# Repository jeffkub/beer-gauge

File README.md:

# beer-gauge
Digital scale with display for weighing beer left in a keg/kegerator

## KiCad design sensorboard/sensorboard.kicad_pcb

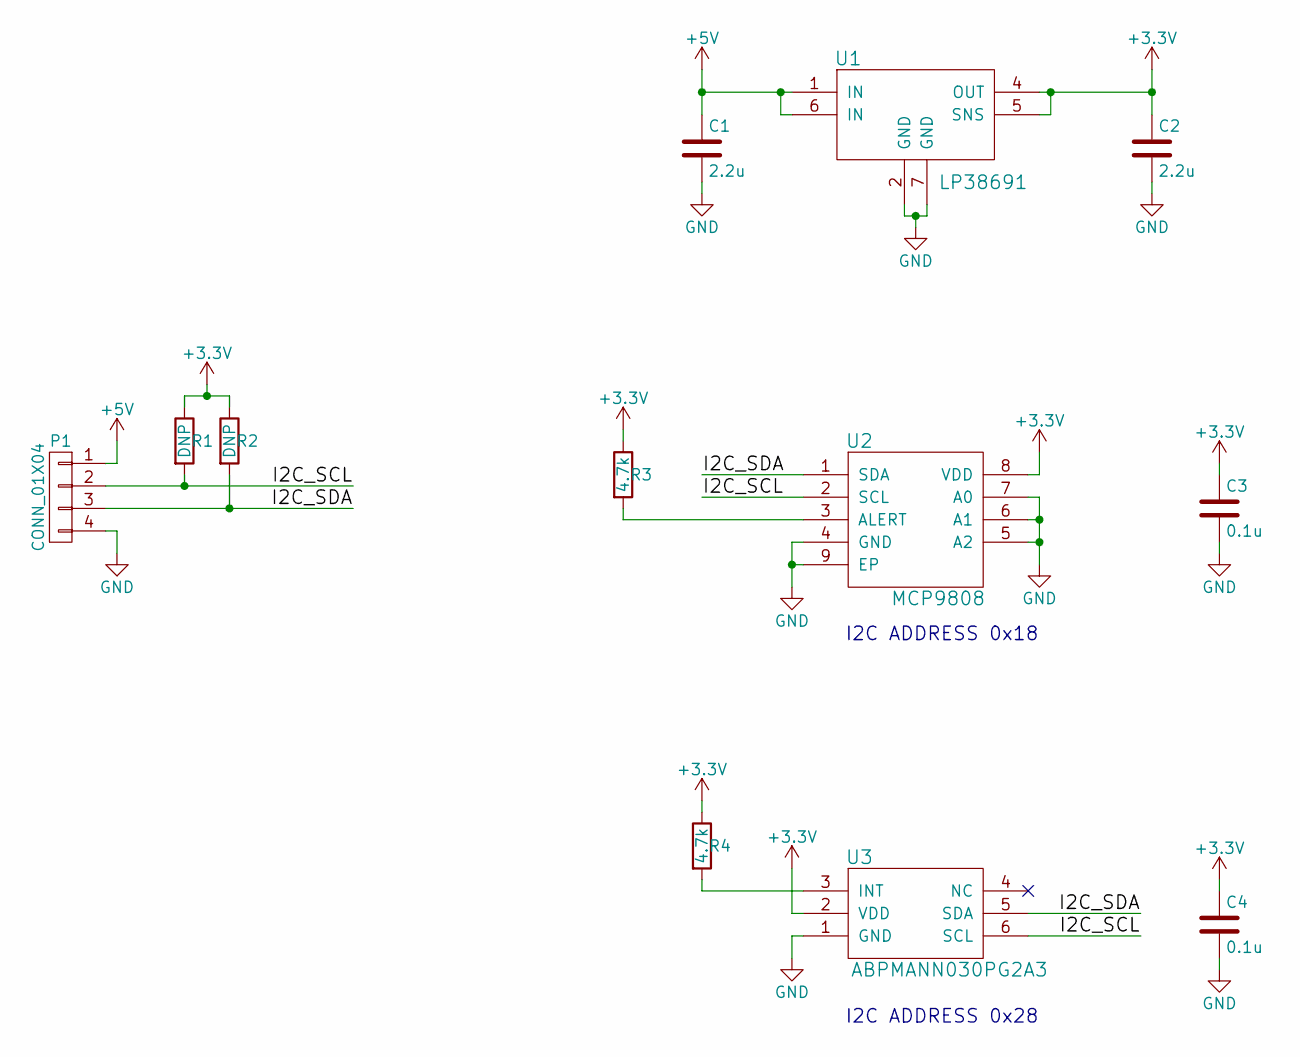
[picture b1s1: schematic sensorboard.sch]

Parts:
C1, C2: 2.2u; C_0603
C3, C4: 0.1u; C_0603
P1: CONN_01X04; 0855025005
R1, R2: DNP; R_0603
R3, R4: 4.7k; R_0603
U1: LP38691; DFN-6-1EP_3x3mm_Pitch0.95mm
U2: MCP9808; DFN-8-1EP_3x2mm_Pitch0.5mm
U3: ABPMANN030PG2A3

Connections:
+3V3: C2.1, C3.1, C4.1, R1.1, R2.1, R3.1, R4.1, U1.4 (OUT), U1.5 (SNS), U2.8 (VDD), U3.2 (VDD)
+5V: C1.1, P1.1, U1.1 (IN), U1.6 (IN)
/I2C_SCL: P1.2, R1.2, U2.2 (SCL), U3.6 (SCL)
/I2C_SDA: P1.3, R2.2, U2.1 (SDA), U3.5 (SDA)
GND: C1.2, C2.2, C3.2, C4.2, P1.4, U1.2 (GND), U1.7 (GND), U2.4 (GND), U2.5 (A2), U2.6 (A1), U2.7 (A0), U2.9 (EP), U3.1 (GND)
unnamed: R3.2, U2.3 (ALERT)
unnamed: R4.2, U3.3 (INT)

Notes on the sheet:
I2C ADDRESS 0x18
I2C ADDRESS 0x28

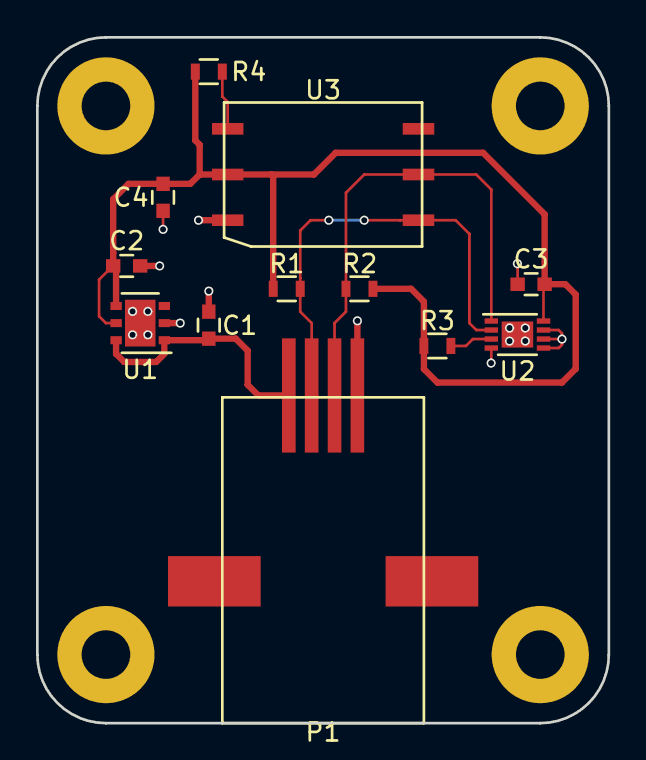
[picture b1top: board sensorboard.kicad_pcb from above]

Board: 2 copper layers, 31.8 x 38.1 mm, 12 parts (0 on the bottom side), 7 nets.

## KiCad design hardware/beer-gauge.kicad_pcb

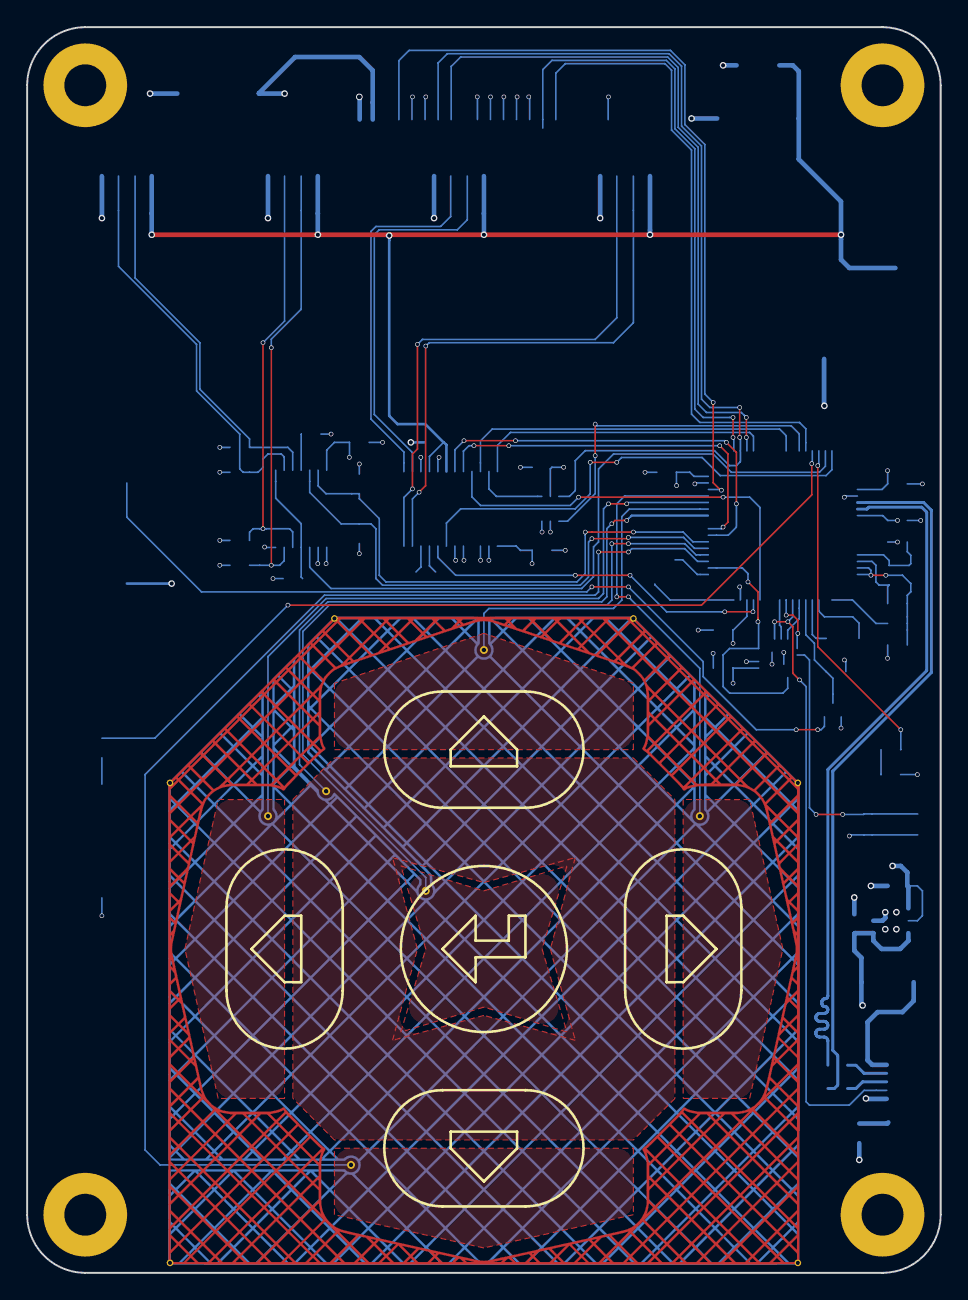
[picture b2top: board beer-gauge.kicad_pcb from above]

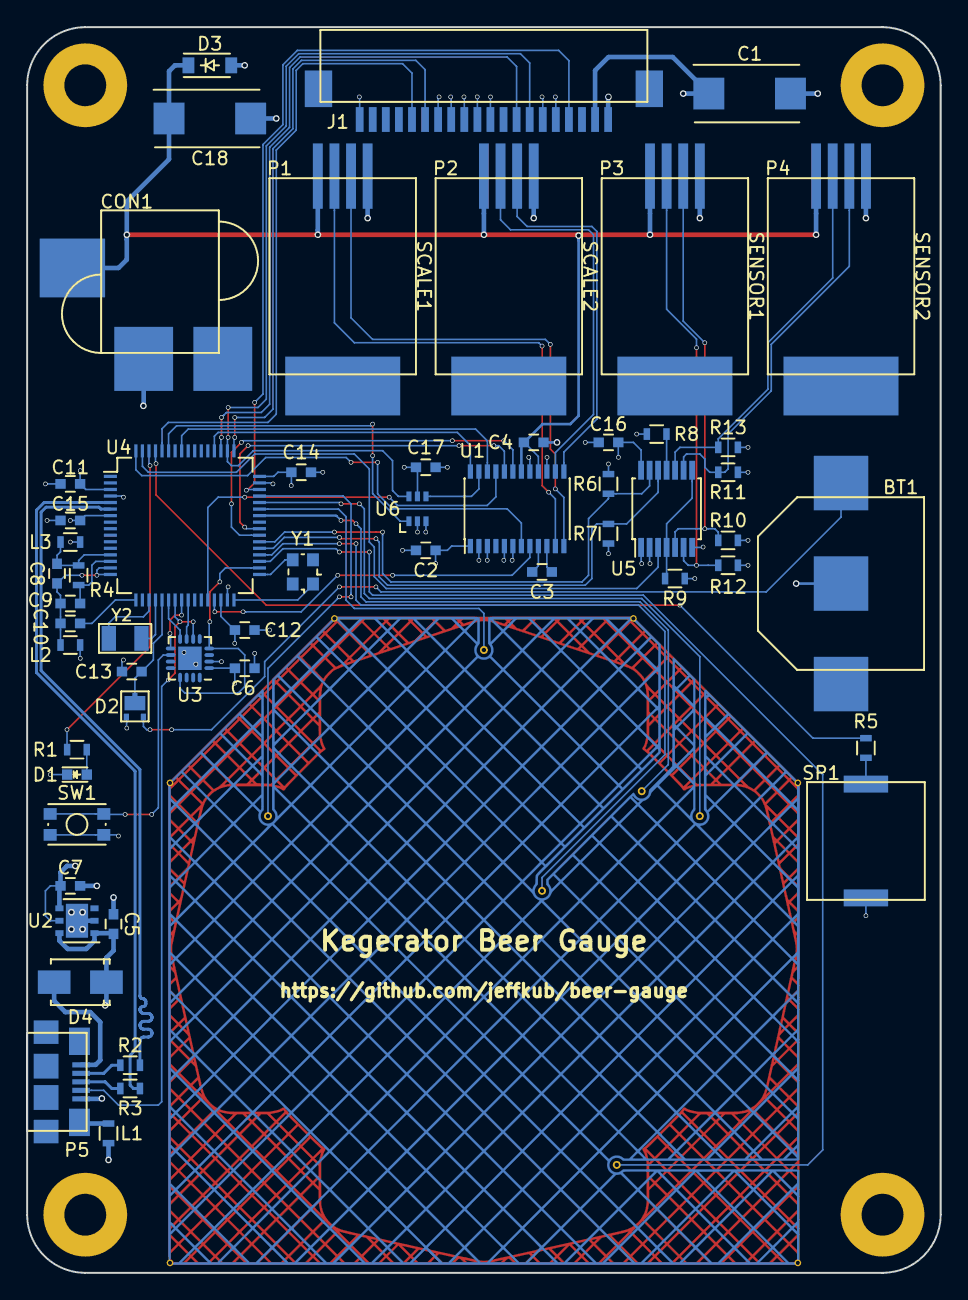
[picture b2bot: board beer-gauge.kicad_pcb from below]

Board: 4 copper layers, 69.8 x 95.2 mm, 62 parts (56 on the bottom side), 64 nets.

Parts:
BT1: Battery; BK-885
C1: 220u; TantalC_SizeD_EIA-7343_Reflow
C2, C3, C4, C6, C9, C10, C11, C12, C13, C14, C16, C17: 0.1u; C_0603
C5, C7, C8, C15: 2.2u; C_0603
C18: 100u; TantalC_SizeD_EIA-7343_Reflow
CON1: BARREL_JACK; PJ-070AH-SMT
D1: LED; LED_0603
D2: PMEG4010CPA; SOT1061
D3: DDZ6V2B; SOD-123
D4: S1B; SMA_Standard
J1: OLED_MODULE; 0522712069
L1, L3: 600 Ohm/100 MHz; R_0603
L2: 600 Ohm/100 Mhz; R_0603
P1, P2, P3, P4: CONN_01X04; 0855135016
P5: USB_OTG; 10118192
R1, R4, R5: 470; R_0603
R2, R3: 33; R_0603
R6, R7, R8, R9, R10, R11, R12, R13: 4.7k; R_0603
SP1: PIEZO; PKMCS
SW1: SW_PUSH; SW_SPST_KMR2
U1: ADS1232; TSSOP-24_4.4x7.8mm_Pitch0.65mm
U2: LP38691; DFN-6-1EP_3x3mm_Pitch0.95mm
U3: MKL02Z32; QFN-16-1EP_3x3mm_Pitch0.5mm
U4: MK20DX256VLH7; LQFP-64_10x10mm_Pitch0.5mm
U5: TCA9543A; TSSOP-14_4.4x5mm_Pitch0.65mm
U6: SN74LVC1G58; SC-70-6
W1, W2, W3, W4, W5, W6: TEST_1P; PadVia
Y1: 16 MHz; Crystal_SMD_2520_4Pads
Y2: 32.768 kHz; ABS07

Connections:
+3V3: C1.1, C2.1, C6.1, C7.1, C11.1, C12.1, C14.1, C15.1, C16.1, C17.1, D2.2, J1.2, L3.1, R6.1, R7.1, R8.1, R9.1, R10.1, R11.1, R12.1, R13.1, U1.1, U2.4, U2.5, U3.1, U4.3, U4.7, U4.30, U4.48, U5.14, U6.5
+5V: C4.1, C5.1, C18.1, CON1.1, D3.1, D4.1, P1.1, P2.1, P3.1, P4.1, U1.16, U1.18, U2.1, U2.6
/Teensy/0: U1.19, U4.39
/Teensy/1: U1.20, U4.40
/Teensy/2: U1.22, U4.57
/Teensy/3: U1.21, U4.28
/Teensy/4: U1.8, U4.29
/Teensy/5: U1.7, U4.64
/Teensy/6: R5.2, U4.61
/Teensy/7: U4.59, U6.1
/Teensy/8: J1.16, U4.60
/Teensy/9: J1.4, U4.46
/Teensy/10: J1.15, U4.49
/Teensy/11: J1.8, U4.51
/Teensy/12: U1.24, U4.52
/Teensy/13: J1.7, U4.50, U6.6
/Teensy/15/A1: U4.43, W1.1
/Teensy/16/A2: U4.35, W2.1
/Teensy/17/A3: U4.36, W5.1
/Teensy/18/A4: R6.2, U4.38, U5.13
/Teensy/19/A5: R7.2, U4.37, U5.12
/Teensy/20/A6: R1.1, U4.62
/Teensy/21/A7: U4.63, U5.3
/Teensy/22/A8: U4.44, W3.1
/Teensy/23/A9: U4.45, W4.1
/Teensy/25: U4.42, W6.1
/Teensy/AREF: C9.1, R4.1, U4.14
/Teensy/ID: P5.4, U3.6, U4.23
/Teensy/RESET_B: U3.4, U3.13, U4.34
/Teensy/SWD_CLK: U3.8, U4.22
/Teensy/SWD_DIO: U3.7, U4.25
/Teensy/USB_D+: R3.1, U4.5
/Teensy/USB_D-: R2.1, U4.6
GND: BT1.2, C1.2, C2.2, C4.2, C5.2, C6.2, C7.2, C11.2, C12.2, C13.2, C14.2, C15.2, C16.2, C17.2, C18.2, CON1.2, D1.1, D3.2, J1.1, J1.5, J1.6, J1.10, J1.11, J1.12, J1.13, J1.14, J1.20, L1.2, L2.1, P1.4, P2.4, P3.4, P4.4, P5.5, SP1.2, SW1.1, U1.2, U1.3, U1.5, U1.6, U1.15, U1.17, U2.2, U2.7, U3.2, U3.17, U4.4, U4.31, U4.47, U5.1, U5.2, U5.7, U6.2, U6.3
unnamed: BT1.1, D2.1
unnamed: C3.1, U1.9
unnamed: C3.2, U1.10
unnamed: C8.1, L3.2, R4.2, U4.13
unnamed: C10.1, U4.17
unnamed: C8.2, C9.2, C10.2, L2.2, U4.15, U4.16
unnamed: C13.1, D2.3, U4.21
unnamed: D1.2, R1.2
unnamed: D4.2, P5.1
unnamed: L1.1, P5.6
unnamed: P1.2, U1.11
unnamed: P1.3, U1.12
unnamed: P2.2, U1.14
unnamed: P2.3, U1.13
unnamed: P3.2, R12.2, U5.6
unnamed: P3.3, R10.2, U5.5
unnamed: P4.2, R13.2, U5.10
unnamed: P4.3, R11.2, U5.9
unnamed: P5.2, R2.2
unnamed: P5.3, R3.2
unnamed: R5.1, SP1.1
unnamed: R8.2, U5.11
unnamed: R9.2, U5.4, U5.8
unnamed: SW1.2, U3.10
unnamed: U1.23, U6.4
unnamed: U3.9, U4.24
unnamed: U4.19, Y2.1
unnamed: U4.20, Y2.2
unnamed: U4.32, Y1.1
unnamed: U4.33, Y1.2

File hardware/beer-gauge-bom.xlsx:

| Ref | Description | Source | Part # | Qty | Footprint | Notes
 | BT1 | HOLDER COIN CELL 12MM SMD | DigiKey | BK-885-CT-ND | 1 | footprint:BK-885
 | CON1 | CONN PWR JACK 2.0X5.5MM SMD | DigiKey | CP-070AHPJCT-ND | 1 | footprint:PJ-070AH-SMT
 | C1 | CAP TANT 220UF 16V 10% 2917 | DigiKey | 399-10429-1-ND | 1 | Capacitors_Tantalum_SMD:TantalC_SizeD_EIA-7343_Reflow
 | C2-C4,C6, C9-C14,C16,C17 | 0.10µF ±10% 25V X7R Ceramic Capacitor | DigiKey | 311-1341-1-ND | 12 | Capacitors_SMD:C_0603
 | C5,C7,C8,C15 | 2.2µF ±10% 10V X7R Ceramic Capacitor | DigiKey | 311-1797-1-ND | 4 | Capacitors_SMD:C_0603
 | C18 | CAP TANT 100UF 10V 20% 2917 | DigiKey | 399-3772-1-ND | 1 | Capacitors_Tantalum_SMD:TantalC_SizeD_EIA-7343_Reflow
 | D1 | LED RED CLEAR 0603 SMD | DigiKey | 754-1123-1-ND | 1 | LEDs:LED_0603
 | D2 | DIODE ARRAY SCHOTTKY 40V 3HUSON | DigiKey | 568-6524-1-ND | 1 | footprint:SOT1061
 | D3 | DIODE ZENER 6.2V 500MW SOD123 | DigiKey | DDZ6V2BDICT-ND | 1 | Diodes_SMD:SOD-123
 | D4 | DIODE GEN PURP 100V 1A SMA | DigiKey | S1B-FDICT-ND | 1 | Diodes_SMD:SMA_Standard
 | J1 | CONN FPC BOTTOM 20POS 1.00MM R/A | DigiKey | WM7946CT-ND | 2 | footprint:0522712069
 | L1-L3 | FERRITE BEAD 600 OHM 0603 1LN | DigiKey | 490-1014-1-ND | 3 | Resistors_SMD:R_0603
 | P1-P4 | CONN MOD JACK 4P4C VERT UNSHLD | DigiKey | WM3555CT-ND | 4 | footprint:0855135016
 | P5 | USB - micro B USB 2.0 Receptacle | DigiKey | 609-4613-1-ND | 1 | footprint:10118192
 | R1,R4,R5 | RES SMD 470 OHM 1% 1/10W 0603 | DigiKey | 311-470HRCT-ND | 3 | Resistors_SMD:R_0603
 | R2,R3 | RES SMD 33 OHM 1% 1/10W 0603 | DigiKey | 311-33.0HRCT-ND | 2 | Resistors_SMD:R_0603
 | R6-R13 | RES SMD 4.7K OHM 1% 1/10W 0603 | DigiKey | 311-4.70KHRCT-ND | 8 | Resistors_SMD:R_0603
 | SP1 | BUZZER PIEZO 12.5V 9MM SMD | DigiKey | 490-9647-1-ND | 1 | footprint:PKMCS
 | SW1 | SWITCH TACTILE SPST-NO 0.05A 32V | DigiKey | CKN10284CT-ND | 1 | Buttons_Switches_SMD:SW_SPST_KMR2
 | U1 | IC ADC 24-BIT 10/80SPS 24-TSSOP | DigiKey | 296-25894-1-ND | 1 | Housings_SSOP:TSSOP-24_4.4x7.8mm_Pitch0.65mm
 | U2 | IC REG LDO 3.3V 0.5A 6WSON | DigiKey | 296-42346-1-ND | 1 | Housings_DFN_QFN:DFN-6-1EP_3x3mm_Pitch0.95mm
 | U3 | MKL02 chip pre-programmed with Teensy bootloader | PJRC | IC_MKL02Z32_QFN16 | 1 | Housings_DFN_QFN:QFN-16-1EP_3x3mm_Pitch0.5mm | https://www.pjrc.com/store/ic_mkl02.html
 | U4 | IC MCU 32BIT 256KB FLASH 64LQFP | DigiKey | MK20DX256VLH7-ND | 1 | Housings_QFP:LQFP-64_10x10mm_Pitch0.5mm
 | U5 | IC I2C SW 2CH W/RESET 14TSSOP | DigiKey | 296-42157-1-ND | 1 | Housings_SSOP:TSSOP-14_4.4x5mm_Pitch0.65mm
 | U6 | IC MULT-FUNCTION GATE SC70-6 | DigiKey | 296-15577-1-ND | 1 | TO_SOT_Packages_SMD:SC-70-6
 | Y1 | 16MHz ±15ppm Crystal 8pF | DigiKey | 644-1049-1-ND | 1 | Crystals:Crystal_SMD_2520_4Pads
 | Y2 | 32.768kHz ±20ppm Crystal 12.5pF | DigiKey | 535-9542-1-ND | 1 | footprint:ABS07
 | - | CABLE FFC 1MM TYPE 2 20P100MM | DigiKey | 732-5134-ND | 1
 | - | BATTERY LITHIUM 3V COIN 12.5MM | DigiKey | P033-ND | 1

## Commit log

2016-06-11 Initial commit of KiCad project
2016-06-14 Created TEENSY footprint
2016-06-16 Added subsheet for TEENSY schematic. Working on TEENSY circuit based on online reference design.
2016-06-17 Working on schematic
2016-06-17 Created schematic PDF. Working on BOM.
2016-06-19 Working on BOM.
2016-06-19 Added piezo transducer. Working on footprints
2016-06-19 Working on capacitive touch pad. Added footprint for piezo
2016-06-20 Added footprint for coin cell battery holder and RJ10 jack
2016-06-21 Working on footprints. Exported netlist into layout.
2016-06-22 Finished footprints. Switched to a tantalum cap for the LCD. Changed piezo resistor value to 470 to reduce part count.
2016-06-22 Working on capacitive touch arrow pad layout
2016-06-23 Working on component placement
2016-06-24 Working on PCB layout
2016-06-26 Finished routing traces
2016-06-26 Finished routing the board
2016-06-27 Added RTC battery to BOM. Fixed BOM quantities
2016-06-27 Initial commit of arduino code
2016-06-29 Working on library for ADS1234
2016-06-30 Working on ADC driver library
2016-06-30 Added some silkscreen text. Adjusted soldermask clearance as it was too large.
2016-07-06 Changed OLED display to use SPI interface in schematic
2016-07-06 Updating schematic/BOM to use 2 channel ADC, added I2C switch
2016-07-06 Updating layout with schematic changes
2016-07-07 Finished layout of traces
2016-07-07 Minor fixes to layout
2016-07-08 Added DC jack for 5V input. Updated layout
2016-07-09 Minor tweaks to layout
2016-07-09 Created kicad project and schematic for I2C sensor board
2016-07-09 Finished layout of sensor board
2016-07-09 Updated BOM with sensor board parts
2016-07-09 Minor changes to sensor board layout
2016-07-10 Working on acrylic enclosure design
2016-07-11 Working on acrylic enclosure
2016-07-12 Fixed hatching issue
2016-07-12 Updated pin assignments based on REV2 design
2016-07-13 Split hatched filled arcs into many lines to address DFM problems
2016-07-14 Added a hole for access to programming pushbutton
